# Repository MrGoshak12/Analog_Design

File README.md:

# Analog_Design
Repository for my Analog design projects and Lab works

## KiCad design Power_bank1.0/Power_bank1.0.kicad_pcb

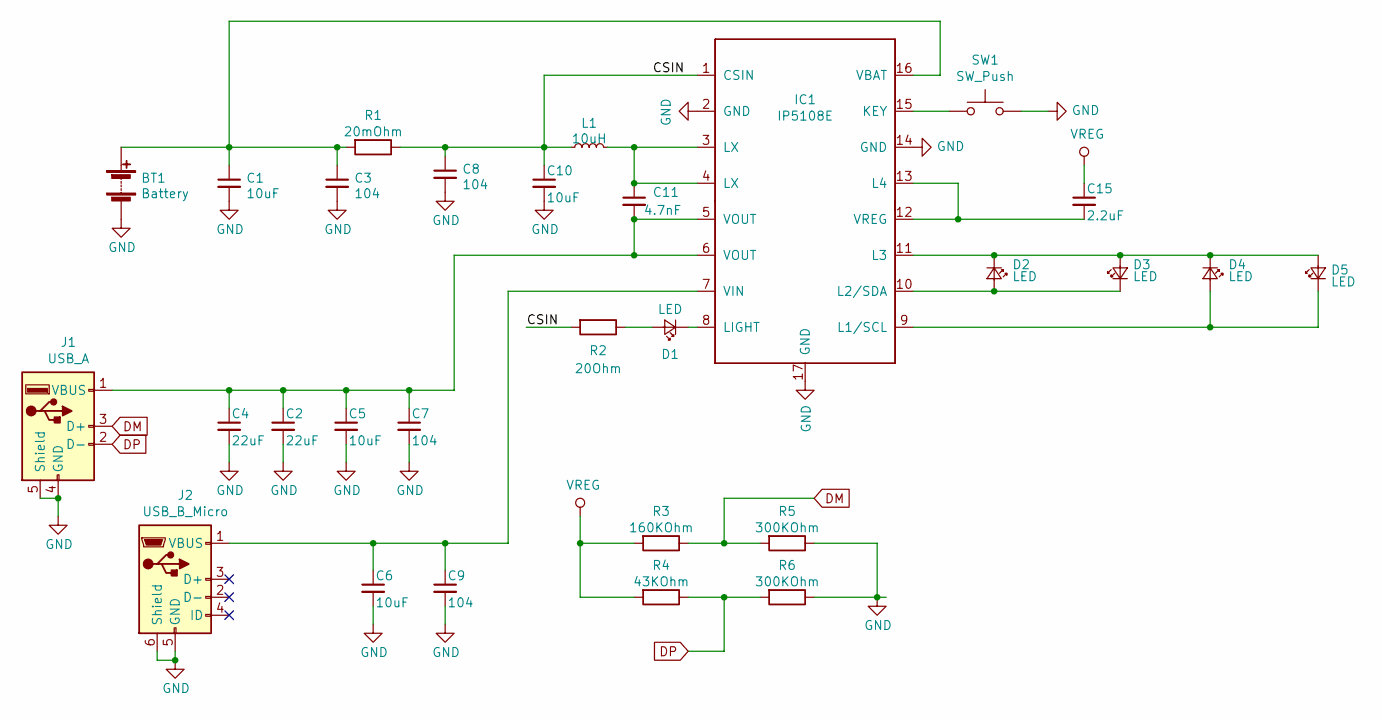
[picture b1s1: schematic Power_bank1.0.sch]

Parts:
BT1: Battery; SolderWirePad_1x02_P3.81mm_Drill0.8mm
C1, C5, C6, C10: 10uF; C_1206_3216Metric_Pad1.42x1.75mm_HandSolder
C2, C4: 22uF; C_1210_3225Metric_Pad1.42x2.65mm_HandSolder
C3, C7, C8, C9: 104; C_0603_1608Metric_Pad1.05x0.95mm_HandSolder
C11: 4.7nF; C_0603_1608Metric_Pad1.05x0.95mm_HandSolder
C15: 2.2uF; C_1206_3216Metric_Pad1.42x1.75mm_HandSolder
D1, D2, D3, D4, D5: LED; LED_1206_3216Metric_Pad1.42x1.75mm_HandSolder
IC1: IP5108E; ESOP-16L_4.55x10.3mm_P1.27mm
J1: USB_A; USB_KLS1-181C
J2: USB_B_Micro; USB_Micro-B_GCT_USB3076-30-A
L1: 10uH; L_1210_3225Metric_Pad1.42x2.65mm_HandSolder
R1: 20mOhm; R_2512_6332Metric_Pad1.52x3.35mm_HandSolder
R2: 20Ohm; R_1206_3216Metric_Pad1.42x1.75mm_HandSolder
R3: 160KOhm; R_0805_2012Metric_Pad1.15x1.40mm_HandSolder
R4: 43KOhm; R_0603_1608Metric_Pad1.05x0.95mm_HandSolder
R5, R6: 300KOhm; R_1206_3216Metric_Pad1.42x1.75mm_HandSolder
SW1: SW_Push; SW_PUSH_6mm_H5mm

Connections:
/CSIN: C8.1, C10.1, IC1.1 (CSIN), L1.1, R1.1, R2.2
DM: J1.3 (D+), R3.1, R5.2
DP: J1.2 (D-), R4.1, R6.2
GND: BT1.2 (-), C1.2, C2.2, C3.2, C4.2, C5.2, C6.2, C7.2, C8.2, C9.2, C10.2, IC1.2 (GND), IC1.14 (GND), IC1.17 (GND), J1.4 (GND), J1.5 (Shield), J2.5 (GND), J2.6 (Shield), R5.1, R6.1, SW1.2
unnamed: BT1.1 (+), C1.1, C3.1, IC1.16 (VBAT), R1.2
unnamed: C6.1, C9.1, IC1.7 (VIN), J2.1 (VBUS)
unnamed: C11.1, IC1.3 (LX), IC1.4 (LX~), L1.2
unnamed: C2.1, C4.1, C5.1, C7.1, C11.2, IC1.5 (VOUT), IC1.6 (VOUT), J1.1 (VBUS)
unnamed: C15.2, IC1.12 (VREG), IC1.13 (L4)
unnamed: D1.1 (K), IC1.8 (LIGHT)
unnamed: D1.2 (A), R2.1
unnamed: D2.1 (K), D3.2 (A), D4.1 (K), D5.2 (A), IC1.11 (L3)
unnamed: D2.2 (A), D3.1 (K), IC1.10 (L2/SDA)
unnamed: D4.2 (A), D5.1 (K), IC1.9 (L1/SCL)
unnamed: IC1.15 (KEY), SW1.1
VREG: C15.1, R3.2, R4.2

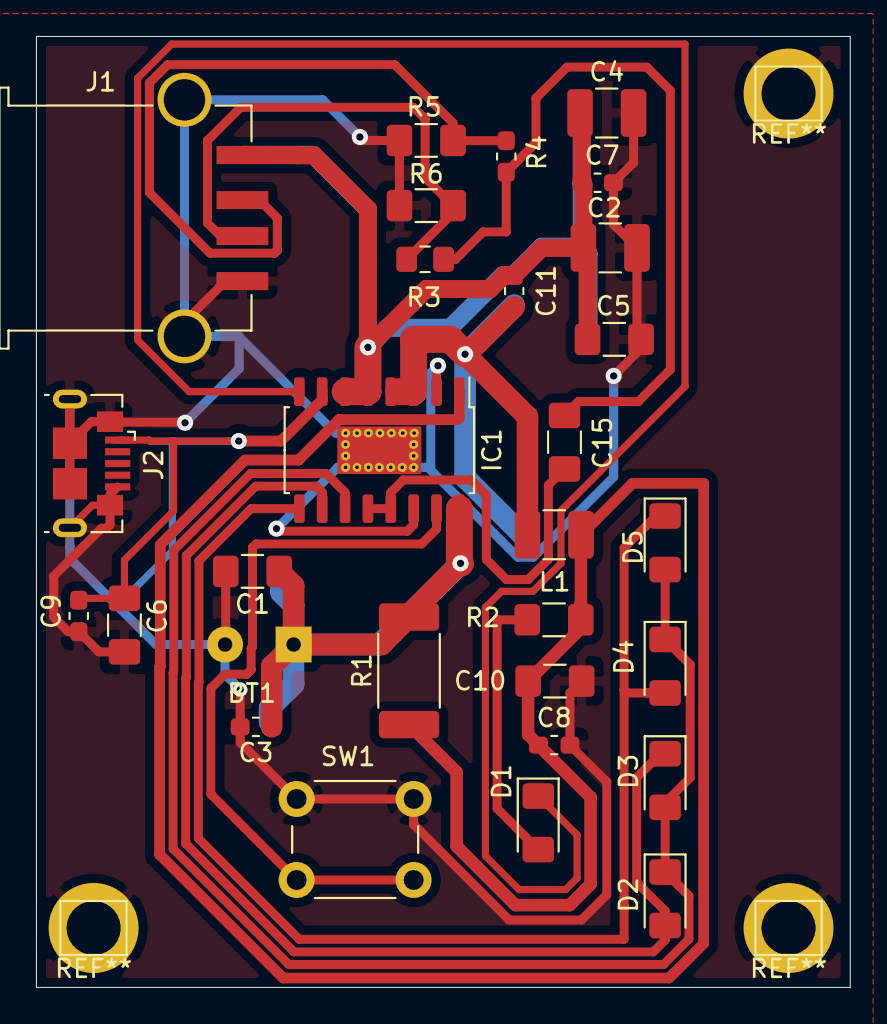
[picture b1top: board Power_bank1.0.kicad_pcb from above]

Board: 2 copper layers, 45.2 x 52.8 mm, 29 parts (0 on the bottom side), 16 nets.

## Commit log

2020-02-17 First lab_work
2020-02-17 Changed name
2020-02-17 new derictory
2020-02-27 Fix amplitude response measure
2020-03-11 Added powerbank1.0 project
2020-03-26 Added corrections
2020-05-28 Coursework in progress...
2020-05-29 Almost 3/4 finished
2020-05-30 almost done
2020-05-31 Coursework done
